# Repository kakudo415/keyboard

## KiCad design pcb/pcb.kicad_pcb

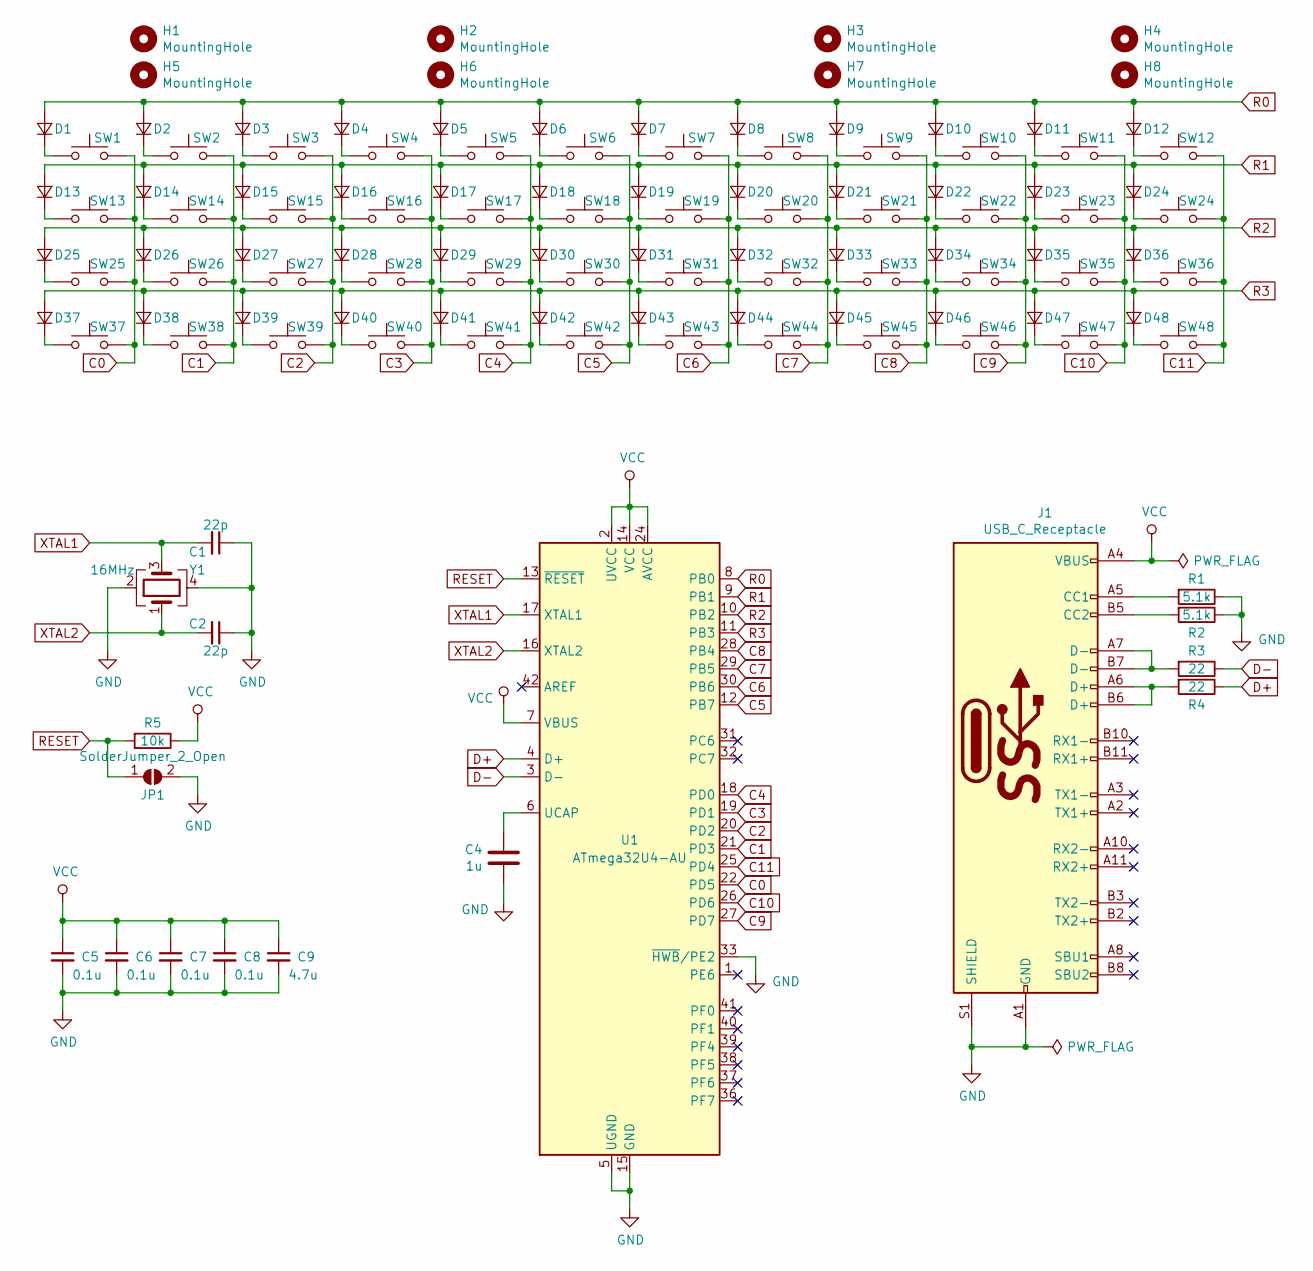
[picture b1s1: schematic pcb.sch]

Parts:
C1, C2: 22p; C_1206_3216Metric_Pad1.42x1.75mm_HandSolder
C4: 1u; C_1206_3216Metric_Pad1.42x1.75mm_HandSolder
C5, C6, C7, C8: 0.1u; C_1206_3216Metric_Pad1.42x1.75mm_HandSolder
C9: 4.7u; C_1206_3216Metric_Pad1.42x1.75mm_HandSolder
D1, D2, D3, D4, D5, D6, D7, D8, D9, D10, D11, D12, D13, D14, D15, D16, D17, D18, D19, D20, D21, D22, D23, D24, D25, D26, D27, D28, D29, D30, D31, D32, D33, D34, D35, D36, D37, D38, D39, D40, D41, D42, D43, D44, D45, D46, D47, D48: D_Small; D_SOD-123F
H1, H2, H3, H4, H5, H6, H7, H8: MountingHole; MountingHole_3.5mm
J1: USB_C_Receptacle; USB-C_Female_CX70M-24P1
JP1: SolderJumper_2_Open; SolderJumper-2_P1.3mm_Open_Pad1.0x1.5mm
R1, R2: 5.1k; R_1206_3216Metric_Pad1.42x1.75mm_HandSolder
R3, R4: 22; R_1206_3216Metric_Pad1.42x1.75mm_HandSolder
R5: 10k; R_1206_3216Metric_Pad1.42x1.75mm_HandSolder
SW1, SW2, SW3, SW4, SW5, SW6, SW7, SW8, SW9, SW10, SW11, SW12, SW13, SW14, SW15, SW16, SW17, SW18, SW19, SW20, SW21, SW22, SW23, SW24, SW25, SW26, SW27, SW28, SW29, SW30, SW31, SW32, SW33, SW34, SW35, SW36, SW37, SW38, SW39, SW40, SW41, SW42, SW43, SW44, SW45, SW46, SW47, SW48: SW_Push; MX_Plate_100H
U1: ATmega32U4-AU; TQFP-44_10x10mm_P0.8mm
Y1: 16MHz; Crystal_SMD_SeikoEpson_FA238-4Pin_3.2x2.5mm_HandSoldering

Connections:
C0: SW1.2, SW13.2, SW25.2, SW37.2, U1.22 (PD5)
C1: SW2.2, SW14.2, SW26.2, SW38.2, U1.21 (PD3)
C2: SW3.2, SW15.2, SW27.2, SW39.2, U1.20 (PD2)
C3: SW4.2, SW16.2, SW28.2, SW40.2, U1.19 (PD1)
C4: SW5.2, SW17.2, SW29.2, SW41.2, U1.18 (PD0)
C5: SW6.2, SW18.2, SW30.2, SW42.2, U1.12 (PB7)
C6: SW7.2, SW19.2, SW31.2, SW43.2, U1.30 (PB6)
C7: SW8.2, SW20.2, SW32.2, SW44.2, U1.29 (PB5)
C8: SW9.2, SW21.2, SW33.2, SW45.2, U1.28 (PB4)
C9: SW10.2, SW22.2, SW34.2, SW46.2, U1.27 (PD7)
C10: SW11.2, SW23.2, SW35.2, SW47.2, U1.26 (PD6)
C11: SW12.2, SW24.2, SW36.2, SW48.2, U1.25 (PD4)
D+: R4.1, U1.4 (D+)
D-: R3.1, U1.3 (D-)
GND: C1.1, C2.1, C4.2, C5.2, C6.2, C7.2, C8.2, C9.2, J1.A1 (GND), J1.A12 (GND), J1.B1 (GND), J1.B12 (GND), J1.S1 (SHIELD), JP1.2 (B), R1.1, R2.1, U1.5 (UGND), U1.15 (GND), U1.23 (GND), U1.33 (~HWB~/PE2), U1.35 (GND), U1.43 (GND), Y1.2, Y1.4
unnamed: C4.1, U1.6 (UCAP)
unnamed: D1.1 (K), SW1.1
unnamed: D2.1 (K), SW2.1
unnamed: D3.1 (K), SW3.1
unnamed: D4.1 (K), SW4.1
unnamed: D5.1 (K), SW5.1
unnamed: D6.1 (K), SW6.1
unnamed: D7.1 (K), SW7.1
unnamed: D8.1 (K), SW8.1
unnamed: D9.1 (K), SW9.1
unnamed: D10.1 (K), SW10.1
unnamed: D11.1 (K), SW11.1
unnamed: D12.1 (K), SW12.1
unnamed: D13.1 (K), SW13.1
unnamed: D14.1 (K), SW14.1
unnamed: D15.1 (K), SW15.1
unnamed: D16.1 (K), SW16.1
unnamed: D17.1 (K), SW17.1
unnamed: D18.1 (K), SW18.1
unnamed: D19.1 (K), SW19.1
unnamed: D20.1 (K), SW20.1
unnamed: D21.1 (K), SW21.1
unnamed: D22.1 (K), SW22.1
unnamed: D23.1 (K), SW23.1
unnamed: D24.1 (K), SW24.1
unnamed: D25.1 (K), SW25.1
unnamed: D26.1 (K), SW26.1
unnamed: D27.1 (K), SW27.1
unnamed: D28.1 (K), SW28.1
unnamed: D29.1 (K), SW29.1
unnamed: D30.1 (K), SW30.1
unnamed: D31.1 (K), SW31.1
unnamed: D32.1 (K), SW32.1
unnamed: D33.1 (K), SW33.1
unnamed: D34.1 (K), SW34.1
unnamed: D35.1 (K), SW35.1
unnamed: D36.1 (K), SW36.1
unnamed: D37.1 (K), SW37.1
unnamed: D38.1 (K), SW38.1
unnamed: D39.1 (K), SW39.1
unnamed: D40.1 (K), SW40.1
unnamed: D41.1 (K), SW41.1
unnamed: D42.1 (K), SW42.1
unnamed: D43.1 (K), SW43.1
unnamed: D44.1 (K), SW44.1
unnamed: D45.1 (K), SW45.1
unnamed: D46.1 (K), SW46.1
unnamed: D47.1 (K), SW47.1
unnamed: D48.1 (K), SW48.1
unnamed: J1.A5 (CC1), R1.2
unnamed: J1.A6 (D+), J1.B6 (D+), R4.2
unnamed: J1.A7 (D-), J1.B7 (D-), R3.2
unnamed: J1.B5 (CC2), R2.2
R0: D1.2 (A), D2.2 (A), D3.2 (A), D4.2 (A), D5.2 (A), D6.2 (A), D7.2 (A), D8.2 (A), D9.2 (A), D10.2 (A), D11.2 (A), D12.2 (A), U1.8 (PB0)
R1: D13.2 (A), D14.2 (A), D15.2 (A), D16.2 (A), D17.2 (A), D18.2 (A), D19.2 (A), D20.2 (A), D21.2 (A), D22.2 (A), D23.2 (A), D24.2 (A), U1.9 (PB1)
R2: D25.2 (A), D26.2 (A), D27.2 (A), D28.2 (A), D29.2 (A), D30.2 (A), D31.2 (A), D32.2 (A), D33.2 (A), D34.2 (A), D35.2 (A), D36.2 (A), U1.10 (PB2)
R3: D37.2 (A), D38.2 (A), D39.2 (A), D40.2 (A), D41.2 (A), D42.2 (A), D43.2 (A), D44.2 (A), D45.2 (A), D46.2 (A), D47.2 (A), D48.2 (A), U1.11 (PB3)
RESET: JP1.1 (A), R5.2, U1.13 (~RESET)
VCC: C5.1, C6.1, C7.1, C8.1, C9.1, J1.A4 (VBUS), J1.A9 (VBUS), J1.B4 (VBUS), J1.B9 (VBUS), R5.1, U1.2 (UVCC), U1.7 (VBUS), U1.14 (VCC), U1.24 (AVCC), U1.34 (VCC), U1.44 (AVCC)
XTAL1: C1.2, U1.17 (XTAL1), Y1.3
XTAL2: C2.2, U1.16 (XTAL2), Y1.1

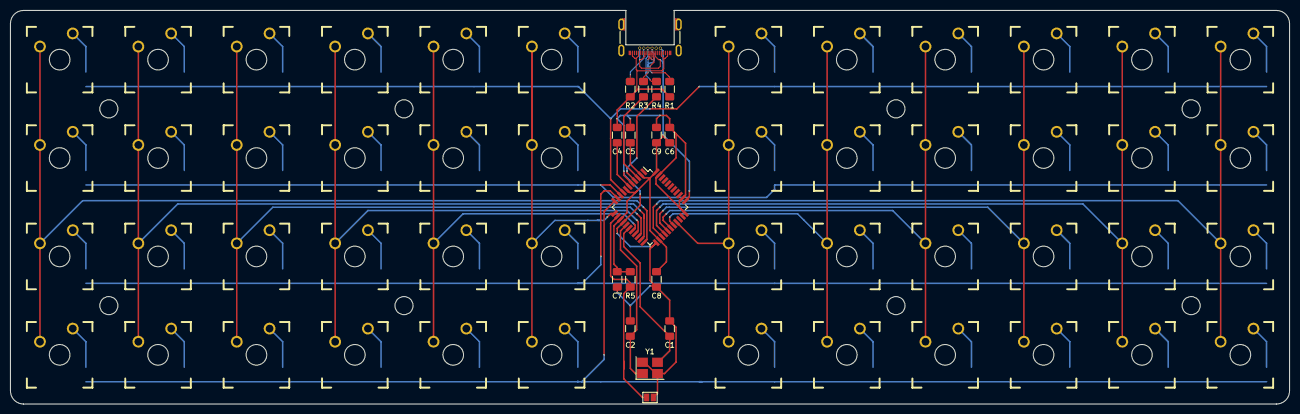
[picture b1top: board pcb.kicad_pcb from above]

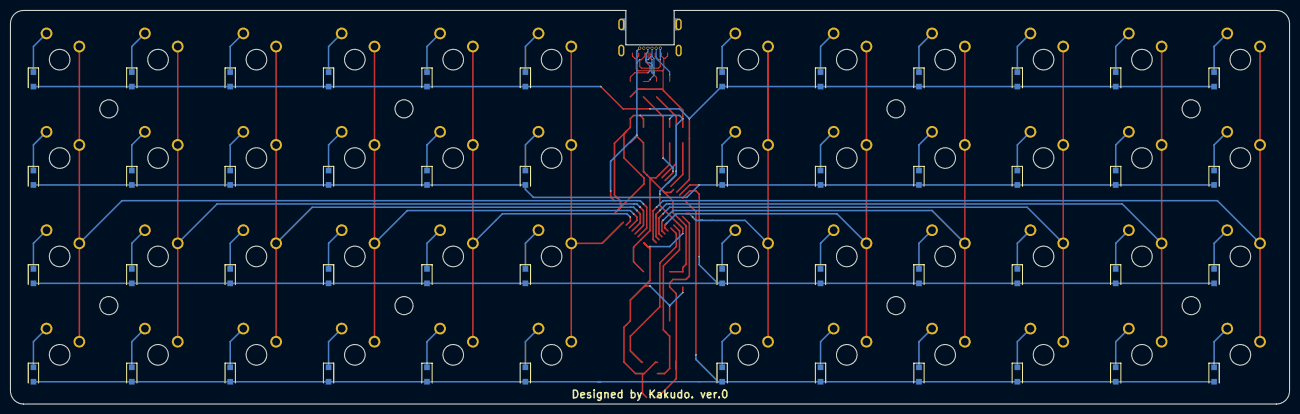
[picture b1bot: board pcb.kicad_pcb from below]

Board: 2 copper layers, 247.7 x 76.2 mm, 121 parts (48 on the bottom side), 76 nets.

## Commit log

2019-06-09 add USB-C Tongue Lib
2019-06-10 add crystal, usb connector
2019-06-22 del USB-C Tounge
2019-06-23 add schematics
2019-06-23 add components
2019-06-26 add USB-C Connector (Hirose CX70M-24P1)
2019-06-26 update USB-C pins
2019-06-29 add PCB & gerber
2019-06-29 add case
2019-06-29 update case cutline (for 遊舎工房)
2019-06-29 fix RGBnized
2019-06-30 add 3d case model
2019-07-09 電圧チカ(何故か1秒周期では無く6秒くらいかかる)
2019-07-09 add Makefile
